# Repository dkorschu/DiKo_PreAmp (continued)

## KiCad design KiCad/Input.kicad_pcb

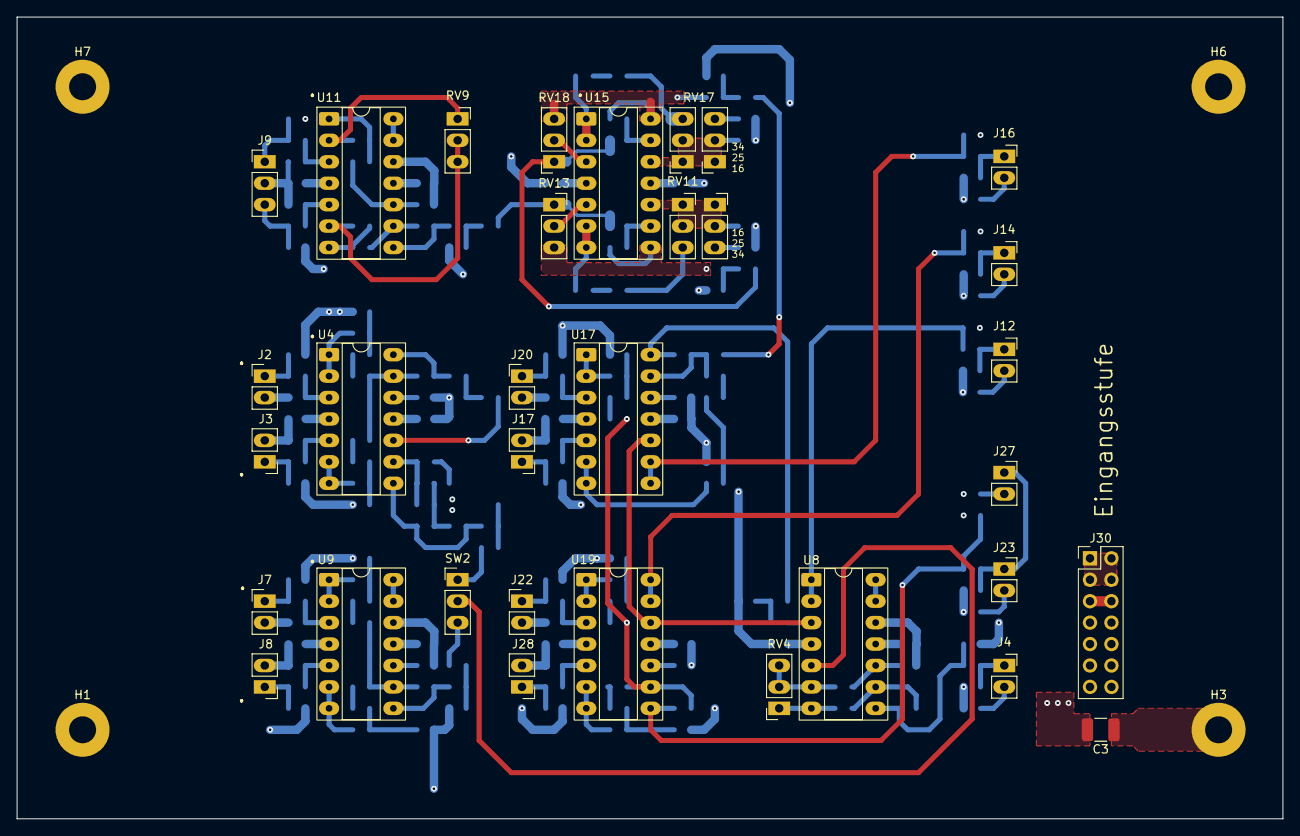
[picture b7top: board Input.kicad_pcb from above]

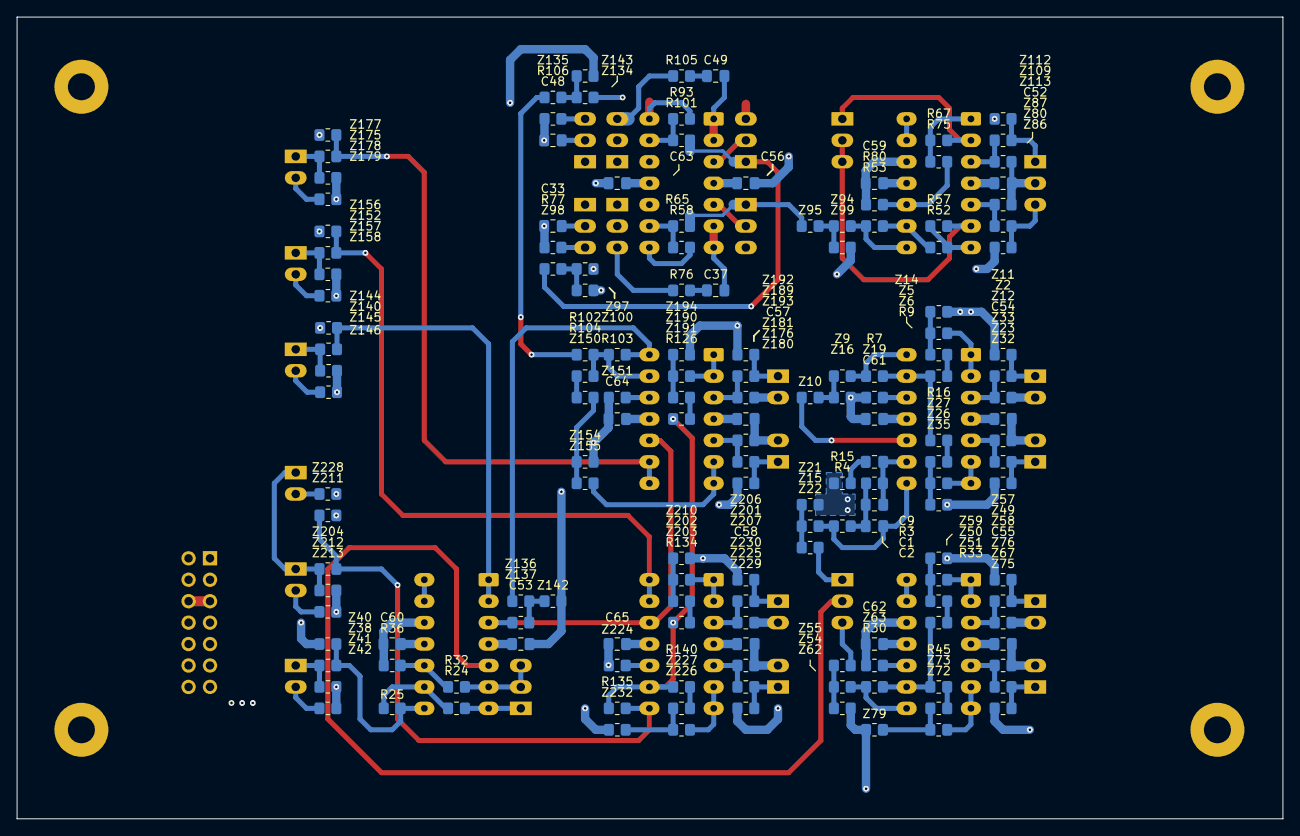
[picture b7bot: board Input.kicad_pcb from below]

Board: 4 copper layers, 150.0 x 95.0 mm, 190 parts (155 on the bottom side), 126 nets.

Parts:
C1: 2n2; C_0805_2012Metric_Pad1.18x1.45mm_HandSolder
C2: 10n; C_0805_2012Metric_Pad1.18x1.45mm_HandSolder
C3: 10n; C_1210_3225Metric_Pad1.33x2.70mm_HandSolder
C9: 47u; C_0805_2012Metric_Pad1.18x1.45mm_HandSolder
C33, C48: 470p; C_0805_2012Metric_Pad1.18x1.45mm_HandSolder
C37, C49: 3n; C_0805_2012Metric_Pad1.18x1.45mm_HandSolder
C52, C53, C54, C55, C56, C57, C58, C59, C60, C61, C62, C63, C64, C65: 100n; C_0805_2012Metric_Pad1.18x1.45mm_HandSolder
H1, H6, H7: MountingHole; MountingHole_3.2mm_M3_Pad
H3: MountingHole_Pad; MountingHole_3.2mm_M3_Pad
J2: R_Phono_In; PinHeader_1x02_P2.54mm_Vertical_LongPads
J3: L_Phono_In; PinHeader_1x02_P2.54mm_Vertical_LongPads
J4: Phono/Line_Out; PinSocket_1x02_P2.54mm_Vertical_LongPads
J7: R_Line_In; PinHeader_1x02_P2.54mm_Vertical_LongPads
J8: L_Line_In; PinHeader_1x02_P2.54mm_Vertical_LongPads
J9: Mic_In; PinHeader_1x03_P2.54mm_Vertical_LongPads
J12, J14, J16, J23, J27: Mic_Effekt_Out; PinSocket_1x02_P2.54mm_Vertical_LongPads
J17: AUX_RET_1; PinHeader_1x02_P2.54mm_Vertical_LongPads
J20: Effekt_In; PinHeader_1x02_P2.54mm_Vertical_LongPads
J22: AUX_RET_2; PinHeader_1x02_P2.54mm_Vertical_LongPads
J28: AUX_RET_3; PinHeader_1x02_P2.54mm_Vertical_LongPads
J30: Conn_02x07_Odd_Even; PinHeader_2x07_P2.54mm_Vertical
R3: 36k; R_0805_2012Metric_Pad1.20x1.40mm_HandSolder
R4: 390k; R_0805_2012Metric_Pad1.20x1.40mm_HandSolder
R7, R9, R16, R25, R30, R33, R45, R52, R53, R57, R67, R75, R80, R102, R103, R104, R126, R134, R135, R140: 10k; R_0805_2012Metric_Pad1.20x1.40mm_HandSolder
R15, R36: 1k; R_0805_2012Metric_Pad1.20x1.40mm_HandSolder
R24: 4k7; R_0805_2012Metric_Pad1.20x1.40mm_HandSolder
R32: 470R; R_0805_2012Metric_Pad1.20x1.40mm_HandSolder
R58, R65, R93, R101: 22k; R_0805_2012Metric_Pad1.20x1.40mm_HandSolder
R76, R77, R105, R106: 6k8; R_0805_2012Metric_Pad1.20x1.40mm_HandSolder
RV4: 50k log; PinSocket_1x03_P2.54mm_Vertical_LongPads
RV9: 10k lin; PinSocket_1x03_P2.54mm_Vertical_LongPads
RV11: 220k log; PinSocket_2x03_P2.54mm_Vertical_LongPads
RV13, RV18: 47k lin; PinSocket_1x03_P2.54mm_Vertical_LongPads
RV17: 220k log; PinSocket_2x03_P2.54mm_Vertical_LongPads_Mirrored
SW2: SW_SPDT; PinHeader_1x03_P2.54mm_Vertical_LongPads
U4, U8, U9, U11, U15, U17, U19: TL074; DIP-14_W7.62mm_Socket_LongPads
Z2, Z5, Z6, Z9, Z10, Z11, Z12, Z14, Z15, Z16, Z19, Z21, Z22, Z23, Z26, Z27, Z32, Z33, Z35, Z38, Z40, Z41, Z42, Z49, Z50, Z51, Z54, Z55, Z57, Z58, Z59, Z62, Z63, Z67, Z72, Z73, Z75, Z76, Z79, Z80, Z86, Z87, Z94, Z95, Z97, Z98, Z99, Z100, Z109, Z112, Z113, Z134, Z135, Z136, Z137, Z140, Z142, Z143, Z144, Z145, Z146, Z150, Z151, Z152, Z154, Z155, Z156, Z157, Z158, Z175, Z176, Z177, Z178, Z179, Z180, Z181, Z189, Z190, Z191, Z192, Z193, Z194, Z201, Z202, Z203, Z204, Z206, Z207, Z210, Z211, Z212, Z213, Z224, Z225, Z226, Z227, Z228, Z229, Z230, Z232: R_0805_2012Metric_Pad1.20x1.40mm_HandSolder

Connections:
9V_GND_I: J30.1, J30.2, J30.3, J30.4
+9V_I: J30.5, J30.6
+15V_I: C52.1, C53.2, C54.2, C55.2, C56.2, C57.2, C58.2, J30.13, J30.14, U4.4 (V+), U8.4 (V+), U9.4 (V+), U11.4 (V+), U15.4 (V+), U17.4 (V+), U19.4 (V+)
-15V_I: C59.2, C60.2, C61.2, C62.2, C63.2, C64.2, C65.2, J30.7, J30.8, U4.11 (V-), U8.11 (V-), U9.11 (V-), U11.11 (V-), U15.11 (V-), U17.11 (V-), U19.11 (V-)
GND_I: C3.2, C33.2, C48.2, C52.2, C53.1, C54.1, C55.1, C56.1, C57.1, C58.1, C59.1, C60.1, C61.1, C62.1, C63.1, C64.1, C65.1, J2.2, J3.2, J7.2, J8.2, J9.2, J17.2, J20.2, J22.2, J28.2, J30.9, J30.10, J30.11, J30.12, R15.1, R36.1, R77.1, R80.1, R106.1, U8.12 (+), U9.12 (+), U11.12 (+), Z11.2, Z12.2, Z14.2, Z16.2, Z19.2, Z21.2, Z32.2, Z33.2, Z35.2, Z40.2, Z41.2, Z42.2, Z57.2, Z58.2, Z59.2, Z62.2, Z63.2, Z75.2, Z76.2, Z79.2, Z86.2, Z87.2, Z99.2, Z100.2, Z112.2, Z113.2, Z142.2, Z143.1, Z144.2, Z145.2, Z146.2, Z151.2, Z154.2, Z156.2, Z157.2, Z158.2, Z177.2, Z178.2, Z179.2, Z180.2, Z181.2, Z192.2, Z193.2, Z194.2, Z206.2, Z207.2, Z210.2, Z211.2, Z212.2, Z213.2, Z224.2, Z228.2, Z229.2, Z230.2, Z232.2
unnamed: C1.2, C2.1, R3.1, R4.2
unnamed: C2.2, R4.1, U4.8, Z15.1
unnamed: C3.1, H3.1
unnamed: C9.1, R15.2
unnamed: C37.1, R76.1
unnamed: C49.1, R105.1
unnamed: J2.1, Z2.1, Z11.1
unnamed: J3.1, Z23.1, Z32.1
unnamed: J4.1, Z38.2, Z41.1
unnamed: J4.2, Z42.1
unnamed: J7.1, Z49.1, Z57.1
unnamed: J8.1, Z67.1, Z75.1
unnamed: J9.1, Z109.1, Z112.1
unnamed: J9.3, Z80.1, Z86.1
unnamed: J12.1, Z140.2, Z145.1
unnamed: J12.2, Z146.1
unnamed: J14.1, Z152.2, Z157.1
unnamed: J14.2, Z158.1
unnamed: J16.1, Z175.2, Z178.1
unnamed: J16.2, Z179.1
unnamed: J17.1, Z176.1, Z180.1
unnamed: J20.1, Z189.1, Z192.1
unnamed: J22.1, Z201.1, Z206.1
unnamed: J23.1, J27.1, Z204.2, Z212.1
unnamed: J23.2, Z213.1
unnamed: J27.2, Z228.1
unnamed: J28.1, Z225.1, Z229.1
unnamed: R7.2, U4.14, Z9.1
unnamed: R9.1, Z6.2
unnamed: R16.1, Z27.2
unnamed: R24.1, RV4.1, U8.7
unnamed: R25.2, U8.8, Z38.1, Z40.1
unnamed: R30.2, U9.8, Z54.1
unnamed: R33.1, Z51.2
unnamed: R45.1, Z73.2
unnamed: R52.1, R57.2, U11.7
unnamed: R53.1, U11.8, Z94.1
unnamed: R58.2, RV13.3, U15.8, Z97.1
unnamed: R65.1, RV13.1, Z95.2
unnamed: R67.1, R75.1, U11.1
unnamed: R76.2, RV11.3
unnamed: R77.2, RV11.4
unnamed: R93.2, RV18.3, U15.14, Z134.1
unnamed: R101.1, RV18.1, Z98.2
unnamed: R102.1, Z135.2
unnamed: R103.2, U17.14, Z136.1
unnamed: R104.1, Z150.1
unnamed: R105.2, RV17.3
unnamed: R106.2, RV17.4
unnamed: R126.2, Z191.2
unnamed: R134.2, Z203.2
unnamed: R135.1, U19.8, Z204.1, Z211.1
unnamed: R140.2, Z227.2
unnamed: SW2.1 (A), Z22.2
unnamed: SW2.2 (B), U8.5 (+)
unnamed: SW2.3 (C), Z55.2
unnamed: U4.3 (+), Z2.2, Z12.1
unnamed: U4.1, U4.2 (-), Z5.1
unnamed: U4.5 (+), Z23.2, Z33.1
unnamed: U4.6 (-), U4.7, Z26.1
unnamed: U4.10 (+), Z10.2
unnamed: C1.1, C9.2, R3.2, U4.9 (-)
unnamed: U4.12 (+), Z19.1
unnamed: R7.1, R9.2, R16.2, U4.13 (-)
unnamed: U8.1, U8.2 (-), Z140.1, Z144.1
unnamed: R32.1, RV4.2, RV4.3, U8.6 (-)
unnamed: R32.2, R36.2, U8.10 (+)
unnamed: R24.2, R25.1, U8.9 (-)
unnamed: U8.13 (-), U8.14
unnamed: U9.3 (+), Z49.2, Z58.1
unnamed: U9.1, U9.2 (-), Z50.1
unnamed: U9.5 (+), Z67.2, Z76.1
unnamed: U9.6 (-), U9.7, Z72.1
unnamed: U9.10 (+), Z63.1
unnamed: R30.1, R33.2, R45.2, U9.9 (-)
unnamed: U9.13 (-), U9.14
unnamed: U11.3 (+), Z109.2, Z113.1
unnamed: R67.2, RV9.1, U11.2 (-)
unnamed: U11.5 (+), Z80.2, Z87.1
unnamed: R57.1, RV9.2, RV9.3, U11.6 (-)
unnamed: R75.2, R80.2, U11.10 (+)
unnamed: R52.2, R53.2, U11.9 (-)
unnamed: U11.13 (-), U11.14
unnamed: RV18.2, U15.3 (+)
unnamed: C49.2, U15.1, U15.2 (-)
unnamed: RV13.2, U15.5 (+)
unnamed: C37.2, U15.6 (-), U15.7
unnamed: C33.1, RV11.1, RV11.2, RV11.5, RV11.6, U15.10 (+)
unnamed: R58.1, R65.2, U15.9 (-)
unnamed: C48.1, RV17.1, RV17.2, RV17.5, RV17.6, U15.12 (+)
unnamed: R93.1, R101.2, U15.13 (-)
unnamed: U17.3 (+), Z189.2, Z193.1
unnamed: U17.1, U17.2 (-), Z190.1
unnamed: U17.5 (+), Z176.2, Z181.1
unnamed: U17.6 (-), U17.7, Z155.2
unnamed: U8.3 (+), U17.10 (+), U19.12 (+), Z137.2
unnamed: U17.8, U17.9 (-), Z175.1, Z177.1
unnamed: U17.12 (+), Z151.1
unnamed: R102.2, R103.1, R104.2, U17.13 (-)
unnamed: U19.3 (+), Z201.2, Z207.1
unnamed: U19.1, U19.2 (-), Z202.1
unnamed: U19.5 (+), Z225.2, Z230.1
unnamed: U19.6 (-), U19.7, Z226.1
unnamed: U19.10 (+), Z224.1
unnamed: R126.1, R134.1, R135.2, R140.1, U19.9 (-)
unnamed: U19.13 (-), U19.14, Z152.1, Z156.1
unnamed: Z9.2, Z10.1, Z16.1
unnamed: Z5.2, Z6.1, Z14.1
unnamed: Z15.2, Z21.1, Z22.1
unnamed: Z26.2, Z27.1, Z35.1
unnamed: Z50.2, Z51.1, Z59.1
unnamed: Z54.2, Z55.1, Z62.1
unnamed: Z72.2, Z73.1, Z79.1
unnamed: Z94.2, Z95.1, Z99.1
unnamed: Z97.2, Z98.1, Z100.1
unnamed: Z134.2, Z135.1, Z143.2
unnamed: Z136.2, Z137.1, Z142.1
unnamed: Z150.2, Z154.1, Z155.1
unnamed: Z190.2, Z191.1, Z194.1
unnamed: Z202.2, Z203.1, Z210.1
unnamed: Z226.2, Z227.1, Z232.1

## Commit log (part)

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2025-09-20 3D_Print_V1
2025-09-20 Altium_V1
2025-09-20 Bachelor_Thesis_V1
2025-09-20 Blockdiagram_V1
2025-09-20 Pictures_V1
2025-09-20 Software_V1.3
2025-09-20 README_V1
2025-10-21 Datasheed
2025-10-21 KiCad
2025-10-21 README
2025-11-10 Einpflegen der Eingangsstufe
2025-11-20 Eingangsstufe update
2025-11-24 Schaltplan Update
2025-12-11 backup update
2025-12-16 Schaltplan und Blockschaltbild Update
2025-12-20 Footprint Update
2025-12-22 PCB Update
2026-01-01 PCB Update Power Supply VU Amp
2026-02-16 PCB Final Update
2026-02-19 common mode chocke Update
2026-02-24 final PCB Update
2026-03-05 Output phasen korrektur durch invertierender verstärker
2026-03-09 Output Stage in phase gebracht
2026-03-16 DRC Update
2026-03-16 Gerber Update
2026-03-22 Bezeichner und BOM Update
2026-04-02 Kicad Einstellungen
2026-04-03 Einganststufe Update
2026-04-14 RIAA Spice
2026-04-19 phono aktulisert
2026-05-03 EQ Output Update
2026-05-06 Update Outputstage
2026-05-08 Notebook update
2026-05-10 Update mit Fotos und Blockschaltbild
2026-05-11 Bass Bandpass Update
2026-05-12 update kick
2026-05-13 Mitten Update
2026-05-15 Höhen Update
2026-05-15 Finales Update Ausgangsstufe
2026-05-16 Pegel Update
2026-05-16 VU Test
2026-05-17 VU Update
2026-06-02 Erste mal musik durch geschickt
2026-06-02 Versuchsaufbau
